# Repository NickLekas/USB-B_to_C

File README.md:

# USB B to C
A PCB for replacing USB-B recepticles with a USB-C recepticale in the same footprint of the USB-B port.

V1.1 has been proven to work on a single device. This may or may not work for your device.

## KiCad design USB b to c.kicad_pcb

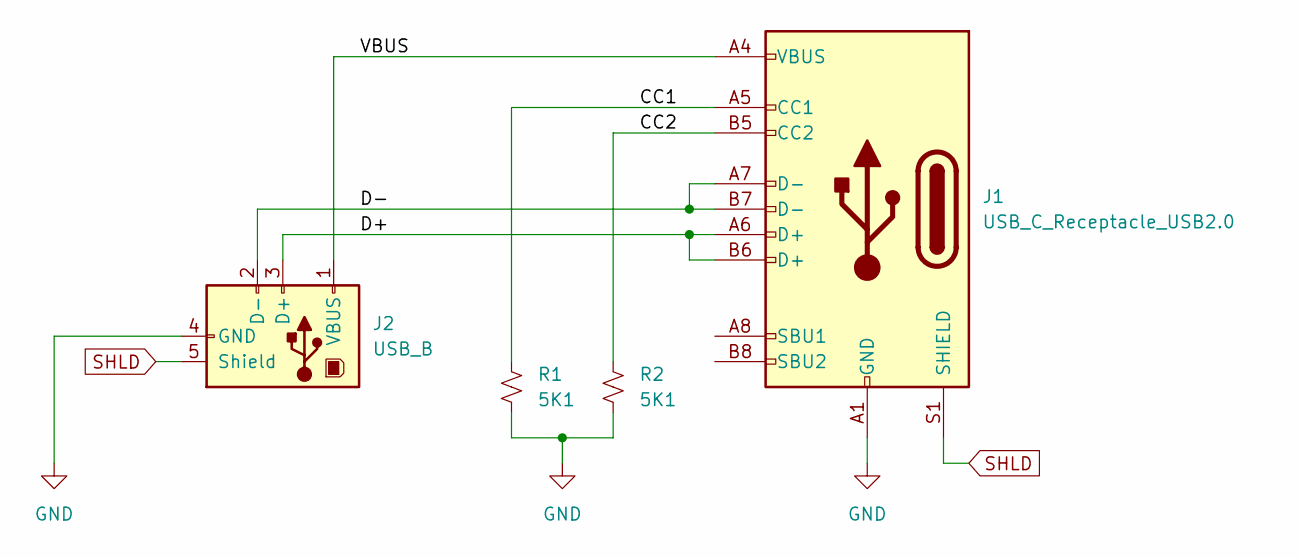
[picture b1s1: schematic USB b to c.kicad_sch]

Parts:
J1: USB_C_Receptacle_USB2.0; USB_C_Receptacle_HRO_TYPE-C-31-M-12
J2: USB_B; USB_B_OST_USB-B1HSxx_Horizontal
R1, R2: 5K1; R_0603_1608Metric

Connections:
/CC1: J1.A5 (CC1), R1.1
/CC2: J1.B5 (CC2), R2.1
/D+: J1.A6 (D+), J1.B6 (D+), J2.3 (D+)
/D-: J1.A7 (D-), J1.B7 (D-), J2.2 (D-)
/VBUS: J1.A4 (VBUS), J1.A9 (VBUS), J1.B4 (VBUS), J1.B9 (VBUS), J2.1 (VBUS)
GND: J1.A1 (GND), J1.A12 (GND), J1.B1 (GND), J1.B12 (GND), J2.4 (GND), R1.2, R2.2
SHLD: J1.S1 (SHIELD), J2.5 (Shield)

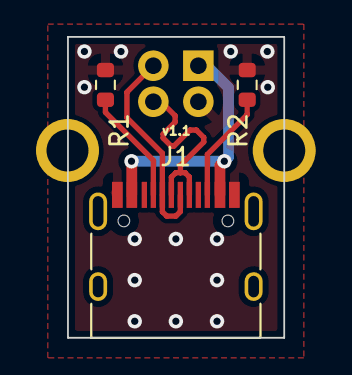
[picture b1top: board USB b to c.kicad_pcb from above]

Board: 2 copper layers, 12.0 x 16.7 mm, 4 parts (0 on the bottom side), 7 nets.

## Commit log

2022-01-30 Added licence
2022-01-30 Rename licence to licence.txt
2022-01-30 Created gitignore
2022-01-30 added more to gitignore
2022-01-30 adding KiCad files
2022-01-30 Added warning about v1.1
2022-01-31 Shifted USB D- for even trace spacing
